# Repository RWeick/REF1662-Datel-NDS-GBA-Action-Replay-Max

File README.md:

# REF1662-Datel-NDS-GBA-Action-Replay-Max
The Kicad files and rom dump for the Datel NDS/GBA Action Replay Max

PCB Thickness: 0.8 mm

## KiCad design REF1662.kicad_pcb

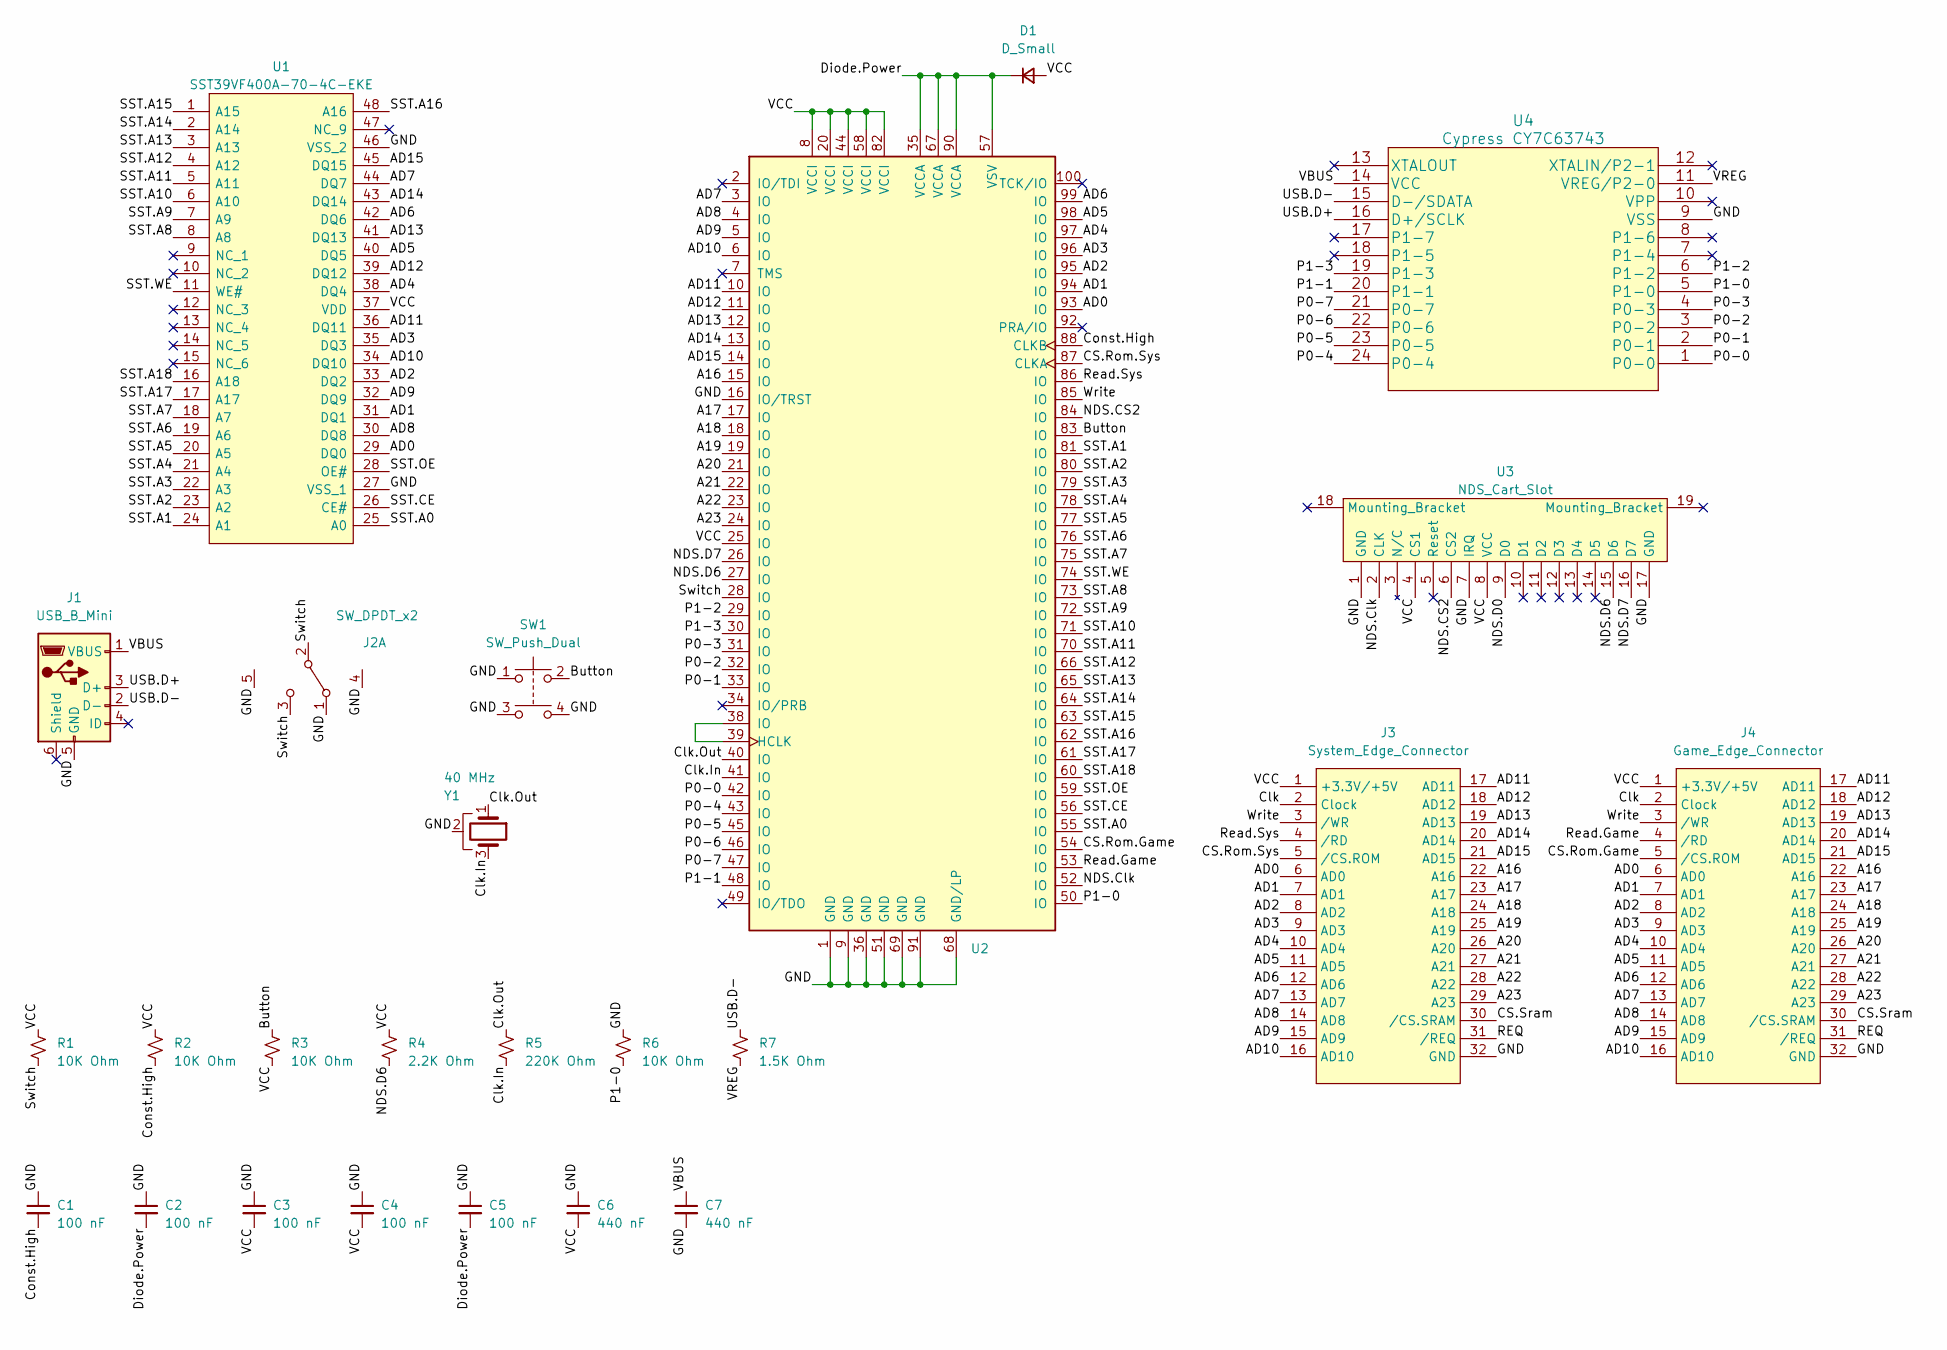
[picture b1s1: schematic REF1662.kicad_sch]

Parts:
C1, C2, C3, C4, C5: 100 nF; AR Max Capacitor
C6, C7: 440 nF; AR Max Capacitor
D1: D_Small; Diode
J1: USB_B_Mini; USB_Mini_B
J2: SW_DPDT_x2; Angled Switch
J3: System_Edge_Connector; Edge Connector
J4: Game_Edge_Connector; Cartridge Slot, GBA
R1, R2, R3, R6: 10K Ohm; AR Max Capacitor
R4: 2.2K Ohm; AR Max Capacitor
R5: 220K Ohm; AR Max Capacitor
R7: 1.5K Ohm; AR Max Capacitor
SW1: SW_Push_Dual; Angled Button
U1: SST39VF400A-70-4C-EKE; sst39vf800a-70-4c-eke; Manufacturer_Part_Number SST39VF200A-70-4C-EKE
U2: EX256-TQ100; TQFP-100_14x14mm_P0.5mm
U3: NDS_Cart_Slot; NDS Slot
U4: Cypress CY7C63743; AR Max Cypress
Y1: 40 MHz; 40MHz Crystal

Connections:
/A16: J3.22 (A16), J4.22 (A16), U2.15 (IO)
/A17: J3.23 (A17), J4.23 (A17), U2.17 (IO)
/A18: J3.24 (A18), J4.24 (A18), U2.18 (IO)
/A19: J3.25 (A19), J4.25 (A19), U2.19 (IO)
/A20: J3.26 (A20), J4.26 (A20), U2.21 (IO)
/A21: J3.27 (A21), J4.27 (A21), U2.22 (IO)
/A22: J3.28 (A22), J4.28 (A22), U2.23 (IO)
/A23: J3.29 (A23), J4.29 (A23), U2.24 (IO)
/AD0: J3.6 (AD0), J4.6 (AD0), U1.29 (DQ0), U2.93 (IO)
/AD1: J3.7 (AD1), J4.7 (AD1), U1.31 (DQ1), U2.94 (IO)
/AD2: J3.8 (AD2), J4.8 (AD2), U1.33 (DQ2), U2.95 (IO)
/AD3: J3.9 (AD3), J4.9 (AD3), U1.35 (DQ3), U2.96 (IO)
/AD4: J3.10 (AD4), J4.10 (AD4), U1.38 (DQ4), U2.97 (IO)
/AD5: J3.11 (AD5), J4.11 (AD5), U1.40 (DQ5), U2.98 (IO)
/AD6: J3.12 (AD6), J4.12 (AD6), U1.42 (DQ6), U2.99 (IO)
/AD7: J3.13 (AD7), J4.13 (AD7), U1.44 (DQ7), U2.3 (IO)
/AD8: J3.14 (AD8), J4.14 (AD8), U1.30 (DQ8), U2.4 (IO)
/AD9: J3.15 (AD9), J4.15 (AD9), U1.32 (DQ9), U2.5 (IO)
/AD10: J3.16 (AD10), J4.16 (AD10), U1.34 (DQ10), U2.6 (IO)
/AD11: J3.17 (AD11), J4.17 (AD11), U1.36 (DQ11), U2.10 (IO)
/AD12: J3.18 (AD12), J4.18 (AD12), U1.39 (DQ12), U2.11 (IO)
/AD13: J3.19 (AD13), J4.19 (AD13), U1.41 (DQ13), U2.12 (IO)
/AD14: J3.20 (AD14), J4.20 (AD14), U1.43 (DQ14), U2.13 (IO)
/AD15: J3.21 (AD15), J4.21 (AD15), U1.45 (DQ15), U2.14 (IO)
/Button: R3.1, SW1.2, U2.83 (IO)
/CS.Rom.Game: J4.5 (/CS.ROM), U2.54 (IO)
/CS.Rom.Sys: J3.5 (/CS.ROM), U2.87 (CLKA)
/CS.Sram: J3.30 (/CS.SRAM), J4.30 (/CS.SRAM)
/Clk: J3.2 (Clock), J4.2 (Clock)
/Clk.In: R5.2, U2.41 (IO), Y1.3
/Clk.Out: R5.1, U2.40 (IO), Y1.1
/Const.High: C1.2, R2.2, U2.88 (CLKB)
/Diode.Power: C2.2, C5.2, D1.1 (K), U2.35 (VCCA), U2.57 (VSV), U2.67 (VCCA), U2.90 (VCCA)
/GND: C1.1, C2.1, C3.1, C4.1, C5.1, C6.1, C7.2, J1.5 (GND), J2.1 (A), J2.4 (Case_GND), J2.5 (Case_GND), J3.32 (GND), J4.32 (GND), R6.1, SW1.1, SW1.3, SW1.4, U1.27 (VSS_1), U1.46 (VSS_2), U2.1 (GND), U2.9 (GND), U2.16 (IO/TRST), U2.36 (GND), U2.51 (GND), U2.68 (GND/LP), U2.69 (GND), U2.91 (GND), U3.1 (GND), U3.7 (IRQ), U3.17 (GND), U4.9 (VSS), Y1.2
/NDS.CS2: U2.84 (IO), U3.6 (CS2)
/NDS.Clk: U2.52 (IO), U3.2 (CLK)
/NDS.D0: U3.9 (D0)
/NDS.D6: R4.2, U2.27 (IO), U3.15 (D6)
/NDS.D7: U2.26 (IO), U3.16 (D7)
/P0-0: U2.42 (IO), U4.1 (P0-0)
/P0-1: U2.33 (IO), U4.2 (P0-1)
/P0-2: U2.32 (IO), U4.3 (P0-2)
/P0-3: U2.31 (IO), U4.4 (P0-3)
/P0-4: U2.43 (IO), U4.24 (P0-4)
/P0-5: U2.45 (IO), U4.23 (P0-5)
/P0-6: U2.46 (IO), U4.22 (P0-6)
/P0-7: U2.47 (IO), U4.21 (P0-7)
/P1-0: R6.2, U2.50 (IO), U4.5 (P1-0)
/P1-1: U2.48 (IO), U4.20 (P1-1)
/P1-2: U2.29 (IO), U4.6 (P1-2)
/P1-3: U2.30 (IO), U4.19 (P1-3)
/REQ: J3.31 (/REQ), J4.31 (/REQ)
/Read.Game: J4.4 (/RD), U2.53 (IO)
/Read.Sys: J3.4 (/RD), U2.86 (IO)
/SST.A0: U1.25 (A0), U2.55 (IO)
/SST.A1: U1.24 (A1), U2.81 (IO)
/SST.A2: U1.23 (A2), U2.80 (IO)
/SST.A3: U1.22 (A3), U2.79 (IO)
/SST.A4: U1.21 (A4), U2.78 (IO)
/SST.A5: U1.20 (A5), U2.77 (IO)
/SST.A6: U1.19 (A6), U2.76 (IO)
/SST.A7: U1.18 (A7), U2.75 (IO)
/SST.A8: U1.8 (A8), U2.73 (IO)
/SST.A9: U1.7 (A9), U2.72 (IO)
/SST.A10: U1.6 (A10), U2.71 (IO)
/SST.A11: U1.5 (A11), U2.70 (IO)
/SST.A12: U1.4 (A12), U2.66 (IO)
/SST.A13: U1.3 (A13), U2.65 (IO)
/SST.A14: U1.2 (A14), U2.64 (IO)
/SST.A15: U1.1 (A15), U2.63 (IO)
/SST.A16: U1.48 (A16), U2.62 (IO)
/SST.A17: U1.17 (A17), U2.61 (IO)
/SST.A18: U1.16 (A18), U2.60 (IO)
/SST.CE: U1.26 (CE#), U2.56 (IO)
/SST.OE: U1.28 (OE#), U2.59 (IO)
/SST.WE: U1.11 (WE#), U2.74 (IO)
/Switch: J2.2 (B), J2.3 (C), R1.2, U2.28 (IO)
/USB.D+: J1.3 (D+), U4.16 (D+/SCLK)
/USB.D-: J1.2 (D-), R7.1, U4.15 (D-/SDATA)
/VBUS: C7.1, J1.1 (VBUS), U4.14 (VCC)
/VCC: C3.2, C4.2, C6.2, D1.2 (A), J3.1 (+3.3V/+5V), J4.1 (+3.3V/+5V), R1.1, R2.1, R3.2, R4.1, U1.37 (VDD), U2.8 (VCCI), U2.20 (VCCI), U2.25 (IO), U2.44 (VCCI), U2.58 (VCCI), U2.82 (VCCI), U3.4 (CS1), U3.8 (VCC)
/VREG: R7.2, U4.11 (VREG/P2-0)
/Write: J3.3 (/WR), J4.3 (/WR), U2.85 (IO)
unnamed: U2.38 (IO), U2.39 (HCLK)

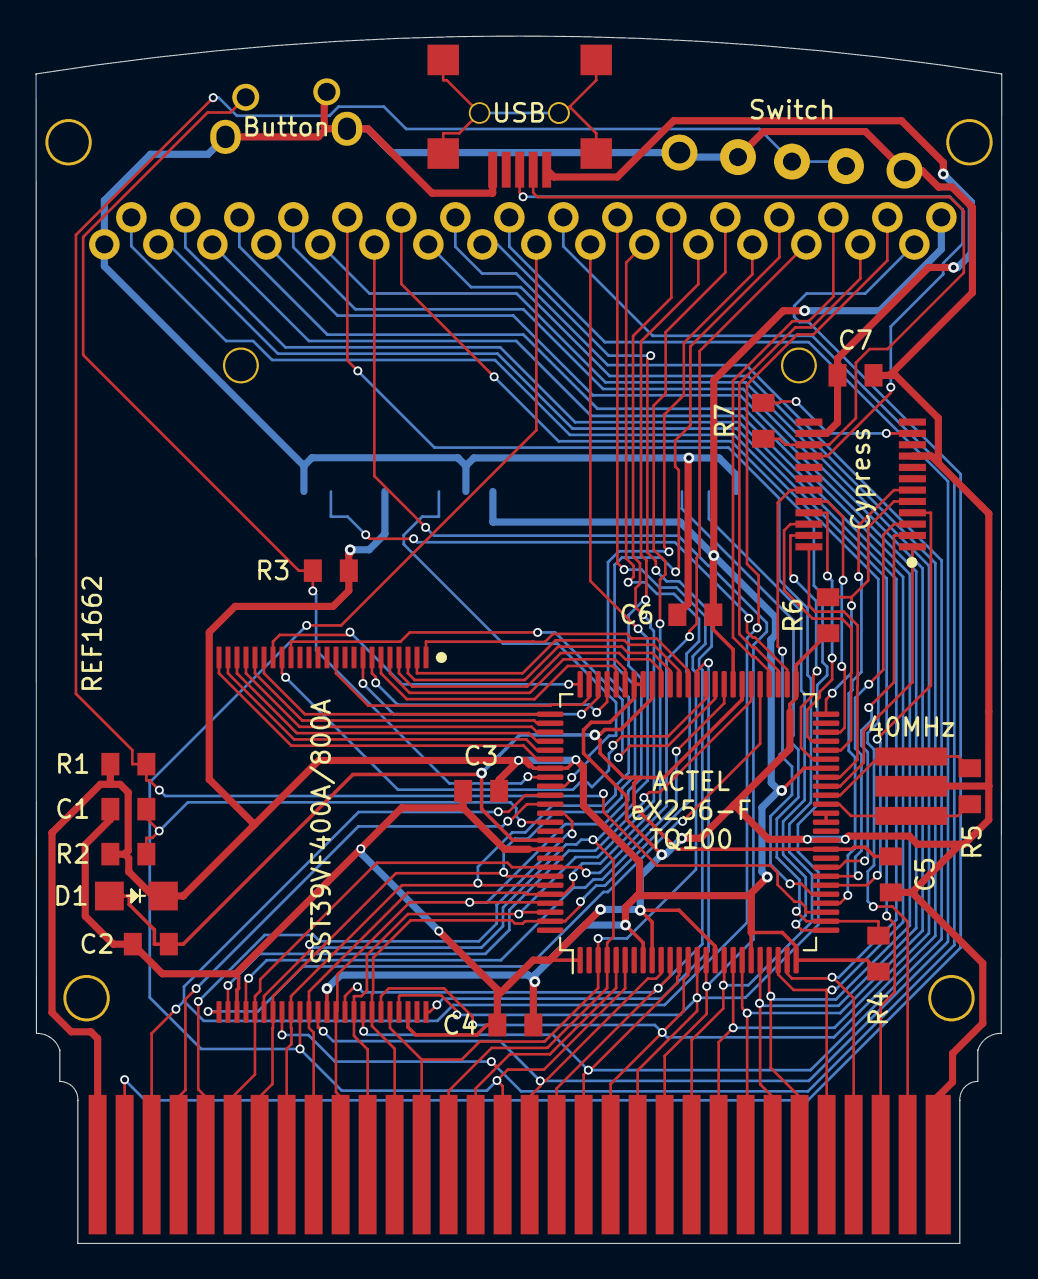
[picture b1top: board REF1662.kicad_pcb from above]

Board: 2 copper layers, 53.6 x 67.1 mm, 26 parts (0 on the bottom side), 83 nets.

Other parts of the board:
DrillHoles: AR MAX Drill Holes
